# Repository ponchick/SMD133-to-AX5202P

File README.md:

# SMD133-to-AX5202P

Adapter PCB from the SMD133 mapper IC to the MMC3 AX5202P.

Several cartridge projects are designed for the AX5202P, but that chip is hard to find, whereas the SMD133 is easier to obtain. This board lets you use the SMD133 in those projects.

Russian version: [`README.ru.md`](README.ru.md)

## Jumper configuration

### `K5K7`

The **K5K7** jumper (on SMD133A the corresponding pin is labeled **K5K6**, on SMD133B — **K5K7**) selects which **additional** register block is active on the SMD133.

- If the jumper is **closed**, the range `$5000–$5005` is used.
- If the jumper is **open** (left open), the range depends on the SMD133 variant:
  - SMD133A → `$6000–$6005`
  - SMD133B → `$7000–$7005`

**Note:** With the jumper open, the chip’s internal pull-down holds the pin to GND. If you want to drive this signal from an external source (for example, from the cartridge PCB), solder to the matching pad on the board and do not bridge the jumper. A closed jumper, conversely, pulls the pin to VCC.  
If you are not planning to experiment with the SMD133, the simplest approach is to leave the jumper unsoldered — this does not affect MMC3 mapper operation.

### `CPU_A1` and `CPU_A12`

The AX5202P does not have these pins, but the SMD133 does.  
These jumpers let you either bring in external address-line signals (for example, from the cartridge PCB) or tie them to ground.

- **Close the jumpers** — the corresponding SMD133 pins are forced to GND. This yields behaviour close to authentic MMC3.
- **Leave them open** — you can feed `CPU_A1` and `CPU_A12` from external circuitry by soldering to the jumper pads.

**Important:** It is not recommended to leave these pins floating (connected neither to ground nor to an external signal). In theory this could lead to unpredictable mapper behaviour, although no one has deliberately verified this.

### `WRAM +CE` and `WRAM WE`

These are **normally closed** jumpers:

- `WRAM +CE` is pulled to `VCC`.
- `WRAM WE` is shorted to the `CPU_RW` signal.

This wiring reproduces AX5202P behaviour, so it is recommended to leave the jumpers as-is.  
If you want to experiment — cut the corresponding jumper.

## License

This project is licensed under **CERN Open Hardware Licence Version 2 – Permissive** (`CERN-OHL-P-2.0`).  
See `LICENSE` for details.

SPDX-License-Identifier: `CERN-OHL-P-2.0`

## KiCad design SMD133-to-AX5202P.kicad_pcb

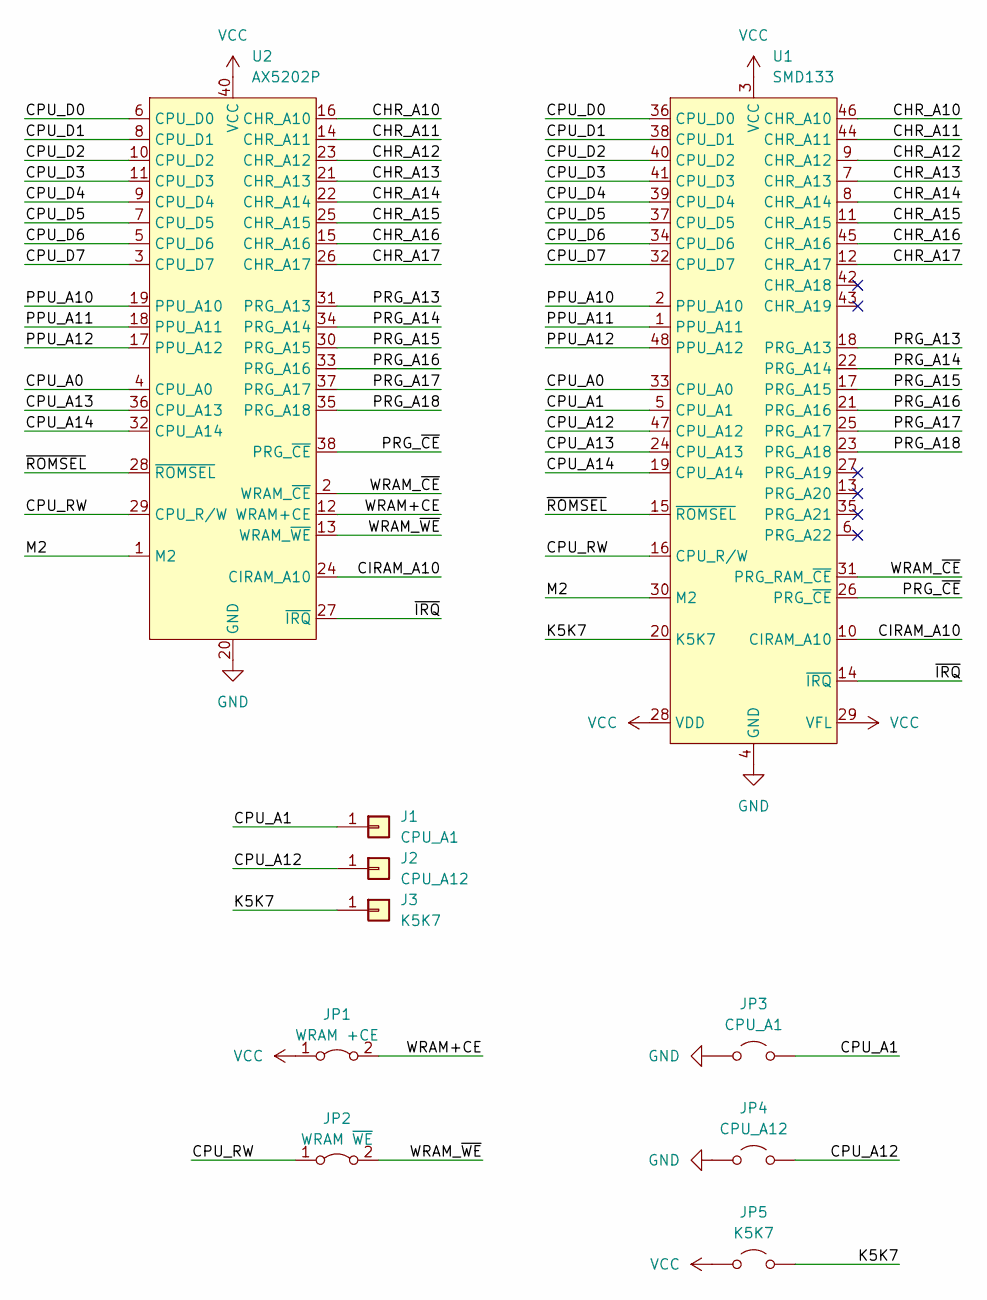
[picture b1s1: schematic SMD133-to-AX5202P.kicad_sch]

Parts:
J1: CPU_A1; TestPoint_THTPad_D2.0mm_Drill1.0mm
J2: CPU_A12; TestPoint_THTPad_D2.0mm_Drill1.0mm
J3: K5K7; TestPoint_THTPad_D2.0mm_Drill1.0mm
JP1: WRAM +CE; SolderJumper-2_P1.3mm_Bridged_Pad1.0x1.5mm
JP2: WRAM ~{WE}; SolderJumper-2_P1.3mm_Bridged_Pad1.0x1.5mm
JP3: CPU_A1; SolderJumper-2_P1.3mm_Open_TrianglePad1.0x1.5mm
JP4: CPU_A12; SolderJumper-2_P1.3mm_Open_TrianglePad1.0x1.5mm
JP5: K5K7; SolderJumper-2_P1.3mm_Open_TrianglePad1.0x1.5mm
U1: SMD133; LQFP-48_7x7mm_P0.5mm
U2: AX5202P; DIP-40_W15.24mm

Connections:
/CHR_A10: U1.46 (CHR_A10), U2.16 (CHR_A10)
/CHR_A11: U1.44 (CHR_A11), U2.14 (CHR_A11)
/CHR_A12: U1.9 (CHR_A12), U2.23 (CHR_A12)
/CHR_A13: U1.7 (CHR_A13), U2.21 (CHR_A13)
/CHR_A14: U1.8 (CHR_A14), U2.22 (CHR_A14)
/CHR_A15: U1.11 (CHR_A15), U2.25 (CHR_A15)
/CHR_A16: U1.45 (CHR_A16), U2.15 (CHR_A16)
/CHR_A17: U1.12 (CHR_A17), U2.26 (CHR_A17)
/CIRAM_A10: U1.10 (CIRAM_A10), U2.24 (CIRAM_A10)
/CPU_A0: U1.33 (CPU_A0), U2.4 (CPU_A0)
/CPU_A1: J1.1, JP3.2 (B), U1.5 (CPU_A1)
/CPU_A12: J2.1, JP4.2 (B), U1.47 (CPU_A12)
/CPU_A13: U1.24 (CPU_A13), U2.36 (CPU_A13)
/CPU_A14: U1.19 (CPU_A14), U2.32 (CPU_A14)
/CPU_D0: U1.36 (CPU_D0), U2.6 (CPU_D0)
/CPU_D1: U1.38 (CPU_D1), U2.8 (CPU_D1)
/CPU_D2: U1.40 (CPU_D2), U2.10 (CPU_D2)
/CPU_D3: U1.41 (CPU_D3), U2.11 (CPU_D3)
/CPU_D4: U1.39 (CPU_D4), U2.9 (CPU_D4)
/CPU_D5: U1.37 (CPU_D5), U2.7 (CPU_D5)
/CPU_D6: U1.34 (CPU_D6), U2.5 (CPU_D6)
/CPU_D7: U1.32 (CPU_D7), U2.3 (CPU_D7)
/CPU_RW: JP2.1 (A), U1.16 (CPU_R/W), U2.29 (CPU_R/W)
/K5K7: J3.1, JP5.2 (B), U1.20 (K5K7)
/M2: U1.30 (M2), U2.1 (M2)
/PPU_A10: U1.2 (PPU_A10), U2.19 (PPU_A10)
/PPU_A11: U1.1 (PPU_A11), U2.18 (PPU_A11)
/PPU_A12: U1.48 (PPU_A12), U2.17 (PPU_A12)
/PRG_A13: U1.18 (PRG_A13), U2.31 (PRG_A13)
/PRG_A14: U1.22 (PRG_A14), U2.34 (PRG_A14)
/PRG_A15: U1.17 (PRG_A15), U2.30 (PRG_A15)
/PRG_A16: U1.21 (PRG_A16), U2.33 (PRG_A16)
/PRG_A17: U1.25 (PRG_A17), U2.37 (PRG_A17)
/PRG_A18: U1.23 (PRG_A18), U2.35 (PRG_A18)
/PRG_~CE: U1.26 (PRG_~CE), U2.38 (PRG_~CE)
/WRAM+CE: JP1.2 (B), U2.12 (WRAM+CE)
/WRAM_~CE: U1.31 (PRG_RAM_~CE), U2.2 (WRAM_~CE)
/WRAM_~WE: JP2.2 (B), U2.13 (WRAM_~WE)
/~IRQ: U1.14 (~IRQ), U2.27 (~IRQ)
/~ROMSEL: U1.15 (~ROMSEL), U2.28 (~ROMSEL)
GND: JP3.1 (A), JP4.1 (A), U1.4 (GND), U2.20 (GND)
VCC: JP1.1 (A), JP5.1 (A), U1.3 (VCC), U1.28 (VDD), U1.29 (VFL), U2.40 (VCC)

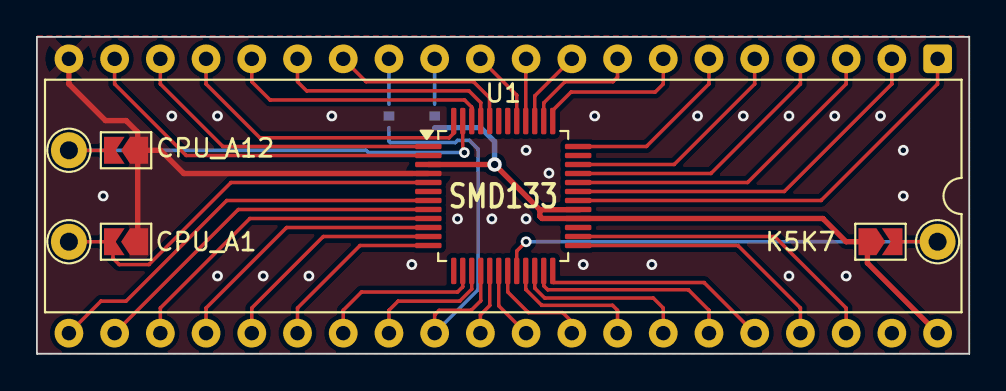
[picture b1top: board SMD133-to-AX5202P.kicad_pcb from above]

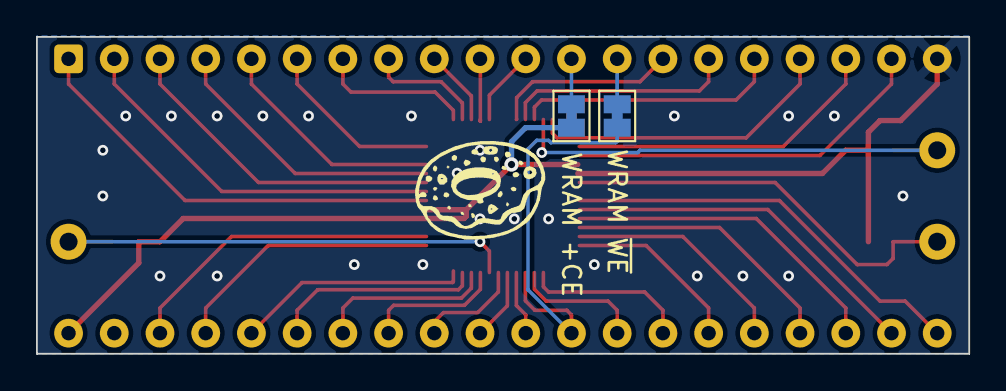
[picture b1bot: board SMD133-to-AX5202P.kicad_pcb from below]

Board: 2 copper layers, 51.8 x 17.6 mm, 11 parts (3 on the bottom side), 42 nets.

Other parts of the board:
LOGO#: LOGO; ponchick

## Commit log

2026-05-02 README: fix jumper K5K7 description
2026-05-03 README: clarify jumper configurations for SMD133.
